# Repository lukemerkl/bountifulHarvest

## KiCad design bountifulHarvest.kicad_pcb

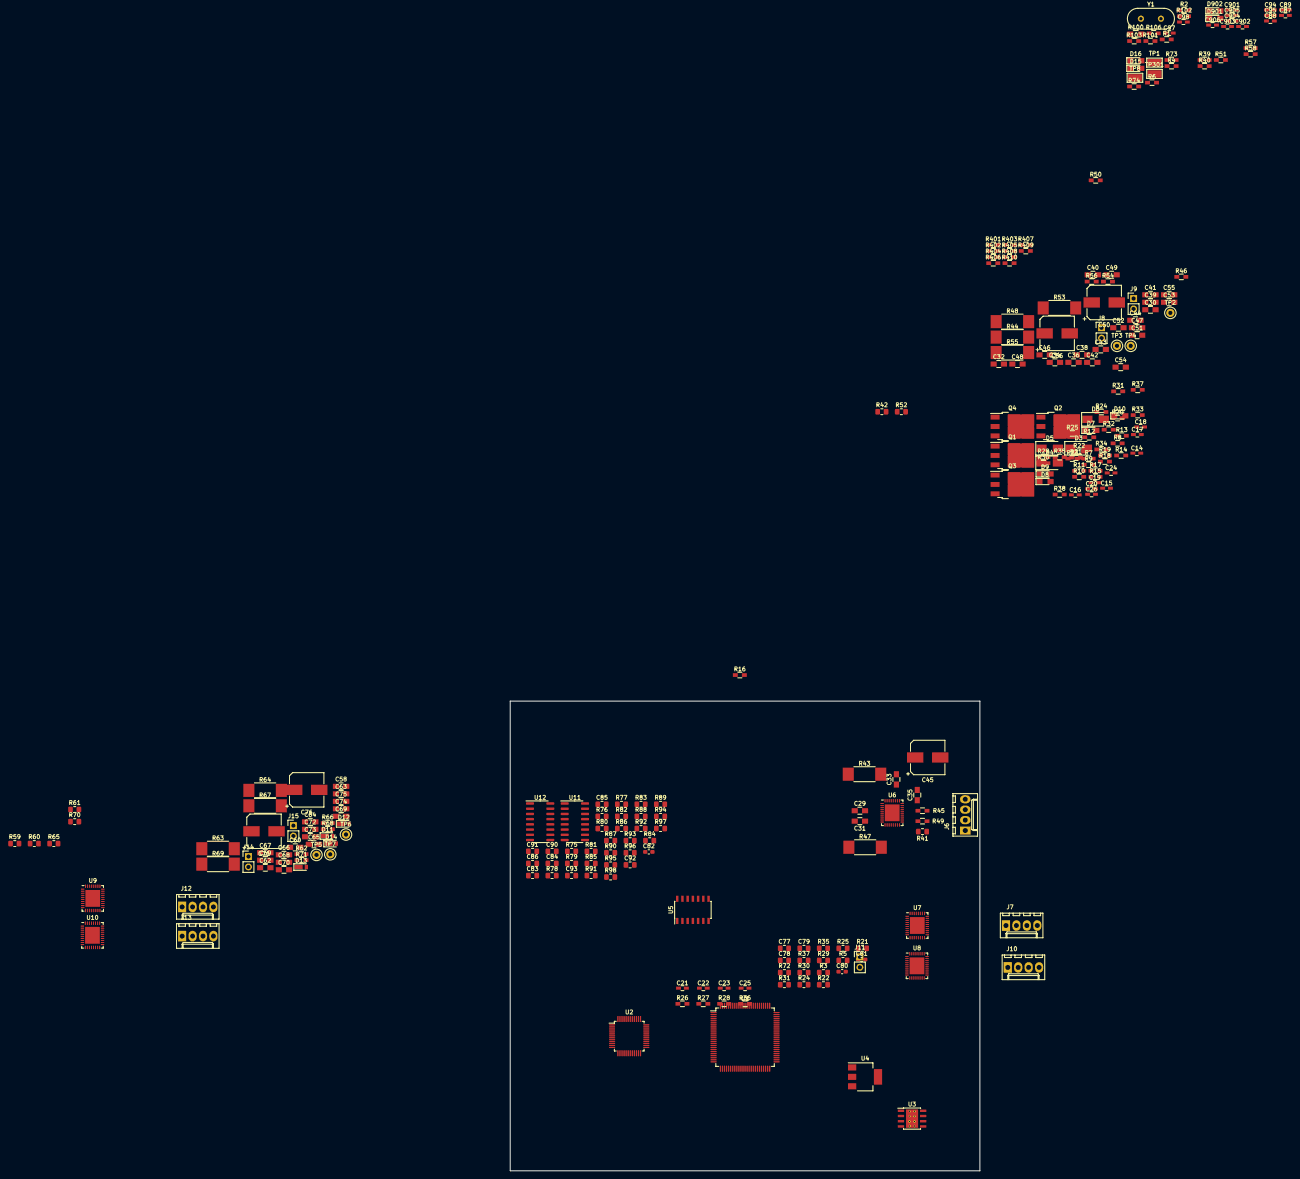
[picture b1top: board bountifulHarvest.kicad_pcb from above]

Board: 4 copper layers, 114.3 x 114.3 mm, 259 parts (0 on the bottom side), 156 nets, no tracks yet.

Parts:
C14, C15, C16, C17, C26: 1nF; C_0603_HandSoldering
C18, C19, C20, C21, C22, C23, C24, C25: 100pF; C_0603_HandSoldering
C29, C30, C38, C58, C62: 4.7uF; C_0805_HandSoldering
C31, C32, C33, C34, C39, C40, C41, C42, C43, C44, C46, C47, C48, C49, C52, C53, C54, C55, C59, C60, C63, C64, C67, C68, C69, C70, C72, C73, C74, C75: 100nF; C_0805_HandSoldering
C35, C36, C51, C65, C66: 22nF; C_0805_HandSoldering
C45, C50, C56, C71, C76: 100uF; CP_Elec_8x10
C77, C78, C79: .1uF; R_0805_2012Metric_Pad1.15x1.40mm_HandSolder
C80, C81, C82: 0.1uF; C_0603_1608Metric_Pad1.05x0.95mm_HandSolder
C83, C84, C85, C86, C90, C91, C92, C93: DNI; C_0805_2012Metric_Pad1.15x1.40mm_HandSolder
C87, C88, C94, C95, C902, C906: 1uF; C_0603_HandSoldering
C89: 0.1uF; C_0603_HandSoldering
C97, C98: 20pF; C_0603_HandSoldering
C901: .1uF; C_0603_HandSoldering
C903, C904: 22uF; C_0603_HandSoldering
C905: 10uF; C_0603_HandSoldering
D3, D4, D5, D6: D_Zener; D_SMA
D7, D8, D9, D10, D15, D16, D901, D902: LED; LED_0805_HandSoldering
D11, D12, D13, D14: DNP; D_TUMD2
J6, J7, J10, J12, J13: CHECK FOOTPRINT; Molex_KK-6410-04_04x2.54mm_Straight
J8, J9, J11, J14, J15: Conn_01x02_Male; Pin_Header_Straight_1x02_Pitch2.54mm
Q1, Q2, Q3, Q4: Q_NMOS_GDSD; TO-252-3_TabPin2
R1, R2, R101, R102, R103: 10K; R_0603_HandSoldering
R3, R5, R21#2, R22#2, R24#2, R35#2, R37#2, R72: 10k; R_0805_2012Metric_Pad1.15x1.40mm_HandSolder
R4, R7, R8, R9, R10, R13, R15, R17, R18, R21, R22, R24, R35, R37, R45, R46, R49, R50, R54, R56, R62, R66, R68, R71, R106: 10k; R_0603_HandSoldering
R6: 3.34k; R_0603_HandSoldering
R11, R12, R14, R16, R39, R40, R51, R57, R58: 10; R_0603_HandSoldering
R19, R401, R402, R403: .05; R_0603_HandSoldering
R20, R73, R74: R; R_0603_HandSoldering
R23, R404, R405, R406, R407, R408, R409, R410: 2k; R_0603_HandSoldering
R25, R29, R30, R31: 50; R_0603_HandSoldering
R25#2, R29#2, R30#2, R31#2: 50; R_0805_2012Metric_Pad1.15x1.40mm_HandSolder
R26, R27, R28, R36: 1k; R_0603_HandSoldering
R32, R33, R34, R38: 33k; R_0603_HandSoldering
R41, R42, R52, R59, R60, R61, R65, R70: R; R_0805_2012Metric_Pad1.15x1.40mm_HandSolder
R43, R44, R47, R48, R53, R55, R63, R64, R67, R69: 120m; R_2512_HandSoldering
R75, R76, R77, R78, R83, R84, R85, R86, R87, R88, R89, R90, R95, R96, R97, R98: DNI; R_0805_2012Metric_Pad1.15x1.40mm_HandSolder
R79, R80, R81, R82, R91, R92, R93, R94: 100; R_0805_2012Metric_Pad1.15x1.40mm_HandSolder
R100: 1M; R_0805_HandSoldering
TP1, TP8, TP301: TestPoint; Test_Point_Keystone_5015_Micro-Minature
TP2, TP3, TP4, TP5, TP6, TP7: TestPoint; Test_Point_Keystone_5000-5004_Miniature
U1: ATmega2560-16AU; TQFP-100_14x14mm_P0.5mm
U2: STM32F303CBTx; LQFP-48_7x7mm_P0.5mm
U3: TPS5430DDA; TI_SO-PowerPAD-8_ThermalVias
U4: AMS1117-3.3; SOT-223-3_TabPin2
U5: LM324A; SOIC-14_3.9x8.7mm_Pitch1.27mm
U6, U7, U8, U9, U10: TMC2130-LA; QFN-36-1EP_5x6mm_P0.5mm_EP3.6x4.1mm
U11, U12: AM26LV32xD; SOIC-16_3.9x9.9mm_P1.27mm
Y1: 16MHz; Crystal_HC49-4H_Vertical

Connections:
+3V3: C26.1, C77.1, C78.1, C79.1, C82.1, C89.1, D16.2, R3.2, R5.2, R20.1, U2.1, U2.24, U2.36, U2.48, U4.2, U5.4, U11.16, U12.16
+5V: C31.1, C32.1, C38.2, C39.1, C59.1, C63.1, C87.1, C88.1, C94.1, C95.1, D15.2, R1.1, R2.1, R4.1, R39.2, R40.2, R41.1, R42.1, R45.1, R46.1, R51.2, R52.1, R54.1, R57.2, R58.2, R59.1, R60.1, R62.1, R65.1, R66.1, R75.1, R76.1, R77.1, R78.1, R87.1, R88.1, R89.1, R90.1, R101.1, R102.1, R103.1, R106.1, TP301.1, U1.10, U1.31, U1.61, U1.80, U4.3, U6.8, U6.26, U6.30, U7.8, U7.26, U7.30, U8.8, U8.25, U8.26, U8.30, U9.8, U9.26, U9.30, U10.8, U10.26, U10.30
+VDC: C33.1, C34.1, C40.1, C41.1, C42.1, C43.1, C44.1, C45.1, C46.1, C47.1, C48.1, C49.1, C50.1, C52.1, C53.1, C54.1, C55.1, C56.1, C60.1, C64.1, C67.1, C68.1, C69.1, C70.1, C71.1, C72.1, C73.1, C74.1, C75.1, C76.1, D3.1, D4.1, D5.1, D6.1, R7.1, R8.1, R9.1, R10.1, U6.16, U6.31, U7.16, U7.31, U8.16, U8.31, U9.16, U9.31, U10.16, U10.31
/Coprocessor/SWDCLK: R21.2, R21#2.2, U2.37
/Coprocessor/SWDIO: R3.1, U2.34
/Coprocessor/X0_A_ENC: U2.32, U11.3
/Coprocessor/X0_B_ENC: U2.33, U11.5
/Coprocessor/X1_A_ENC: U2.29, U11.11
/Coprocessor/X1_B_ENC: U2.30, U11.13
/Coprocessor/Y_A_ENC: U2.40, U12.3
/Coprocessor/Y_B_ENC: U2.41, U12.5
/Coprocessor/Z_A_ENC: U2.10, U2.11, U12.11, U12.13
/Coprocessor/~COP_RESET: C81.1, U2.7
/Coprocessor/~CS: R1.2, R25.1, R25#2.1, R35.2, R35#2.2, U1.78
/Drivers/EN_Y: U1.5, U6.22
/Drivers/STEP_Y: U1.3, U6.6
/Drivers/X_4: R42.2, TP3.1, U7.20, U7.21
/Drivers/Y_4: R41.2, TP2.1, U1.6, U6.20, U6.21
/Drivers/Z_4: R52.2, TP4.1, U8.20, U8.21
/MISO: R30#2.1, U1.21, U6.4, U7.4, U8.4, U9.4, U10.4
/MOSI: R29.1, R29#2.1, R37.2, R37#2.2, U1.22, U6.5, U7.5, U8.5, U9.5, U10.5
/Main Processor/COP_RESET: R101.2, U1.35
/Main Processor/DIR_X: U1.4, U6.7, U7.7
/Main Processor/P_0_I: C21.1, R26.1, U1.97
/Main Processor/P_1_I: C22.1, R27.1, U1.96
/Main Processor/P_2_I: C23.1, R28.1
/Main Processor/P_3_I: C25.1, R36.1
/Main Processor/X2_4: R59.2, TP5.1, U10.20, U10.21
/Main Processor/~CS~_SPI: R2.2, U1.19
/Main Processor/~RESET: R106.2, U1.30
/SCK: R31.1, R31#2.1, R72.2, U1.20, U6.3, U7.3, U8.3, U9.3, U10.3
/Spare/DIAG_0_SPARE: R60.2, R61.1, TP6.1, U9.20
/Spare/DIAG_1_SPARE: R65.2, R70.1, TP7.1, U9.21
/encoders/X0_A_N: C85.2, R81.2, R85.1, U11.1
/encoders/X0_A_P: C85.1, R77.2, R81.1, U11.2
/encoders/X0_B_N: C86.2, R82.2, R86.1, U11.7
/encoders/X0_B_P: C86.1, R78.2, R82.1, U11.6
/encoders/X1_A_N: C83.2, R79.2, R83.1, U11.9
/encoders/X1_A_P: C83.1, R75.2, R79.1, U11.10
/encoders/X1_B_N: C84.2, R80.2, R84.1, U11.15
/encoders/X1_B_P: C84.1, R76.2, R80.1, U11.14
/encoders/Y_A_N: C92.2, R93.2, R97.1, U12.1
/encoders/Y_A_P: C92.1, R89.2, R93.1, U12.2
/encoders/Y_B_N: C93.2, R94.2, R98.1, U12.7
/encoders/Y_B_P: C93.1, R90.2, R94.1, U12.6
/encoders/Z_A_N: C90.2, R91.2, R95.1, U12.9
/encoders/Z_A_P: C90.1, R87.2, R91.1, U12.10
/encoders/Z_B_N: C91.2, R92.2, R96.1, U12.15
/encoders/Z_B_P: C91.1, R88.2, R92.1, U12.14
/peripherals/PERIPH_0: R11.2, U1.15
/peripherals/PERIPH_1: R12.2, U1.16
/peripherals/PERIPH_2: R14.2, U1.17
/peripherals/PERIPH_3: R16.2, U1.18
/peripherals/P_0_SENSE: Q1.3, R19.1, R23.2
GND: C14.2, C15.2, C16.2, C17.2, C18.2, C19.2, C20.2, C21.2, C22.2, C23.2, C24.2, C25.2, C26.2, C29.1, C30.1, C31.2, C32.2, C38.1, C39.2, C41.2, C42.2, C43.2, C44.2, C45.2, C46.2, C47.2, C48.2, C49.2, C50.2, C52.2, C53.2, C54.2, C55.2, C56.2, C58.1, C59.2, C62.1, C63.2, C67.2, C68.2, C69.2, C70.2, C71.2, C72.2, C73.2, C74.2, C75.2, C76.2, C77.2, C78.2, C79.2, C80.2, C81.2, C82.2, C87.2, C88.2, C89.2, C94.2, C95.2, C97.2, C98.2, J8.2, J9.2, J11.2, J14.2, J15.2, R6.2, R13.2, R15.2, R17.2, R18.2, R19.2, R21.1, R21#2.1, R22.2, R22#2.2, R24.2, R24#2.2, R35.1, R35#2.1, R37.1, R37#2.1, R39.1, R40.1, R43.1, R44.1, R47.1, R48.1, R49.2, R50.2, R51.1, R53.1, R55.1, R56.2, R57.1, R58.1, R61.2, R63.1, R64.1, R67.1, R68.2, R69.1, R70.2, R71.2, R72.1, R73.2, R74.2, R83.2, R84.2, R85.2, R86.2, R95.2, R96.2, R97.2, R98.2, R401.2, R402.2, R403.2, R406.2, R407.2, R408.2, R410.2, TP1.1, U1.11, U1.32, U1.62, U1.81, U1.99, U2.8, U2.23, U2.35, U2.47, U3.6, U3.9, U4.1, U5.11, U6.1, U6.11, U6.12, U6.18, U6.24, U6.35, U6.37, U7.1, U7.11, U7.12, U7.18, U7.24, U7.35, U7.37, U8.1, U8.11, U8.12, U8.18, U8.24, U8.35, U8.37, U9.1, U9.11, U9.12, U9.18, U9.24, U9.35, U9.37, U10.1, U10.11, U10.12, U10.18, U10.24, U10.35, U10.37, U11.8, U11.12, U12.8, U12.12
GNDS: C901.2, C902.2, C903.2, C904.2, C905.2, C906.2
unnamed: C14.1, Q1.1, R11.1, R13.1
unnamed: C15.1, Q2.1, R12.1, R15.1
unnamed: C16.1, Q3.1, R14.1, R17.1
unnamed: C17.1, Q4.1, R16.1, R18.1
unnamed: C18.1, R23.1, U5.3
unnamed: C19.1, R404.1, U5.10
unnamed: C20.1, R405.1, U5.12
unnamed: C24.1, R409.1, U5.5
unnamed: C29.2, U6.25
unnamed: C30.2, U7.25
unnamed: C33.2, U6.29
unnamed: C34.2, U7.29
unnamed: C35.1, U6.27
unnamed: C35.2, U6.28
unnamed: C36.1, U7.27
unnamed: C36.2, U7.28
unnamed: C40.2, U8.29
unnamed: C51.1, U8.27
unnamed: C51.2, U8.28
unnamed: C58.2, U9.25
unnamed: C60.2, U9.29
unnamed: C62.2, U10.25
unnamed: C64.2, U10.29
unnamed: C65.1, U9.27
unnamed: C65.2, U9.28
unnamed: C66.1, U10.27
unnamed: C66.2, U10.28
unnamed: C80.1, R20.2, U2.9
unnamed: C97.1, R100.1, U1.34, Y1.1
unnamed: C98.1, R100.2, U1.33, Y1.2
unnamed: D3.2, D7.1, Q1.2
unnamed: D4.2, D8.1, Q2.2
unnamed: D5.2, D9.1, Q3.2
unnamed: D7.2, R7.2
unnamed: D8.2, R8.2
unnamed: D9.2, R9.2
unnamed: D6.2, D10.1, Q4.2
unnamed: D10.2, R10.2
unnamed: D11.1, J12.4, U9.34
unnamed: D11.2, D12.2, R63.2, U9.33
unnamed: D12.1, J12.3, U9.32
unnamed: D13.1, J12.2, U9.15
unnamed: D13.2, D14.2, R67.2, U9.14
unnamed: D14.1, J12.1, U9.13
unnamed: D15.1, R73.1
unnamed: D16.1, R74.1
unnamed: J6.1, U6.13
unnamed: J6.2, U6.15
unnamed: J6.3, U6.32
unnamed: J6.4, U6.34
unnamed: J7.1, U7.13
unnamed: J7.2, U7.15
unnamed: J7.3, U7.32
unnamed: J7.4, U7.34
unnamed: J8.1, U6.36
unnamed: J9.1, U7.36
unnamed: J10.1, U8.13
unnamed: J10.2, U8.15
unnamed: J10.3, U8.32
unnamed: J10.4, U8.34
unnamed: J11.1, U8.36
unnamed: J13.1, U10.13
unnamed: J13.2, U10.15
unnamed: J13.3, U10.32
unnamed: J13.4, U10.34
unnamed: J14.1, U9.36
unnamed: J15.1, U10.36
unnamed: Q2.3, R401.1
unnamed: Q3.3, R402.1
unnamed: Q4.3, R403.1
unnamed: R4.2, R6.1, U3.4
unnamed: R22.1, R22#2.1, U2.44
unnamed: R24.1, R24#2.1, U2.5
unnamed: R25.2, R25#2.2, U2.14
unnamed: R26.2, R32.1, U5.1
unnamed: R27.2, R33.1, U5.8
unnamed: R28.2, R34.1, U5.14
unnamed: R29.2, R29#2.2, U2.15
unnamed: R30.2, R30#2.2, U2.16
unnamed: R31.2, R31#2.2, U2.17
unnamed: R32.2, R406.1, U5.2
unnamed: R33.2, R407.1, U5.9
unnamed: R34.2, R408.1, U5.13
unnamed: R36.2, R38.1, U5.7
unnamed: R38.2, R410.1, U5.6
unnamed: R43.2, U6.33
unnamed: R44.2, U7.33
unnamed: R45.2, R49.1, U6.23
unnamed: R46.2, R50.1, U7.23
unnamed: R47.2, U6.14
unnamed: R48.2, U7.14
unnamed: R53.2, U8.33
unnamed: R54.2, R56.1, U8.23
unnamed: R55.2, U8.14
unnamed: R62.2, R68.1, U9.23
unnamed: R64.2, U10.33
unnamed: R66.2, R71.1, U10.23
unnamed: R69.2, U10.14
unnamed: TP8.1, U3.5
VBUS: C901.1, C902.1, C905.1, D901.2, D902.1, D902.2

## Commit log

2020-11-15 initial push
2020-11-15 Added FET Drivers + PNs. Started Trinamic drivers
2020-12-30 added SPI and sense resistors to stepper driver
2021-01-02 Adding charge pump caps, SPI select, test mode
2021-01-02 Added Caps, finished pinout for dev stepper driver
2021-01-03 Added all stepper circuits. Adding SPI bus to top level sheet. Opened up layout to check connectivity. Errors with footprint libs
2021-01-10 Updated bus connections between drivers at ATMega
2021-01-23 Fixed X,Y,Z driver bus connection. set up spare and X2
2021-10-07 added peripherals
2021-12-04 added RESET and XTAL to atmega2560
2022-01-16 Found error in stepper driver supply
2022-02-24 updated ATMEGA and regulators
2022-03-25 changed ATMEGA vcc to 5V
2022-06-10 added differential RX
2022-06-11 Added motor feedback to stm32. added comms/boot to stm32
2022-06-20 cleaned encoder rx. removed PU from CoP rst. misc other CoP updates
2022-08-05 added endstops
2022-08-07 removed osc from CoP. added signals to atmega
2022-08-07 connected CoP + mP SPI. pushed updated into layout
2022-09-05 added atmega16. finished CoP. need check VBUS <-> ATMEGA supplies
2022-10-01 adding datasheets and references
2022-11-24 added footprints for most of the c,r, and tp's. need new buck
